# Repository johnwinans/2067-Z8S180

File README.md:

# 2067-Z8S180
Z8S180 Breakout Board

- There is a YouTube playlist that discusses the [Z80-Nouveau](https://www.youtube.com/playlist?list=PL3by7evD3F52rUbThUNDYGxNpKFF1HCNT) project for which this board is an early prototype.
- There is a [Verilog/FPGA YouTube tutorial series](https://www.youtube.com/playlist?list=PL3by7evD3F52On-ws9pcdQuEL-rYbNNFB)
- [Verilog examples](https://github.com/johnwinans/Verilog-Examples) that go along with the above YouTube tutorial.
- This board plugs into the [2057-ICE40HX4K-TQ144-breakout](https://github.com/johnwinans/2057-ICE40HX4K-TQ144-breakout) board.

# Useful DOC

- [Schematic PDF](./2067-Z8S180.pdf)
- [Latest release with gerbers](https://github.com/johnwinans/2067-Z8S180/releases/latest)
- [Z80 CPU User Manual UM008011](https://www.zilog.com/docs/z80/um0080.pdf)
- [Z8S180 Manuals](https://zilog.com/index.php?option=com_product&Itemid=26&task=docs&businessLine=&parent_id=139&familyId=19&productId=Z8S180)
    - [Z8S180 DS0060 - Product Specification](https://www.zilog.com/docs/z180/z8s180ps.pdf)
    - [Z80180 UM0050 - User Manual](https://www.zilog.com/docs/z180/um0050.pdf)

# Revision History

## 1.1 Change CPU footprint to make the pads longer
- add mounting holes
- add labels to the pins on J2

## 1.2 Thermal Relief
- reduce spoke widths
- keep polygon pours off the CPU GND pins
- Connect SRAM A20 to GND w/cuttable track

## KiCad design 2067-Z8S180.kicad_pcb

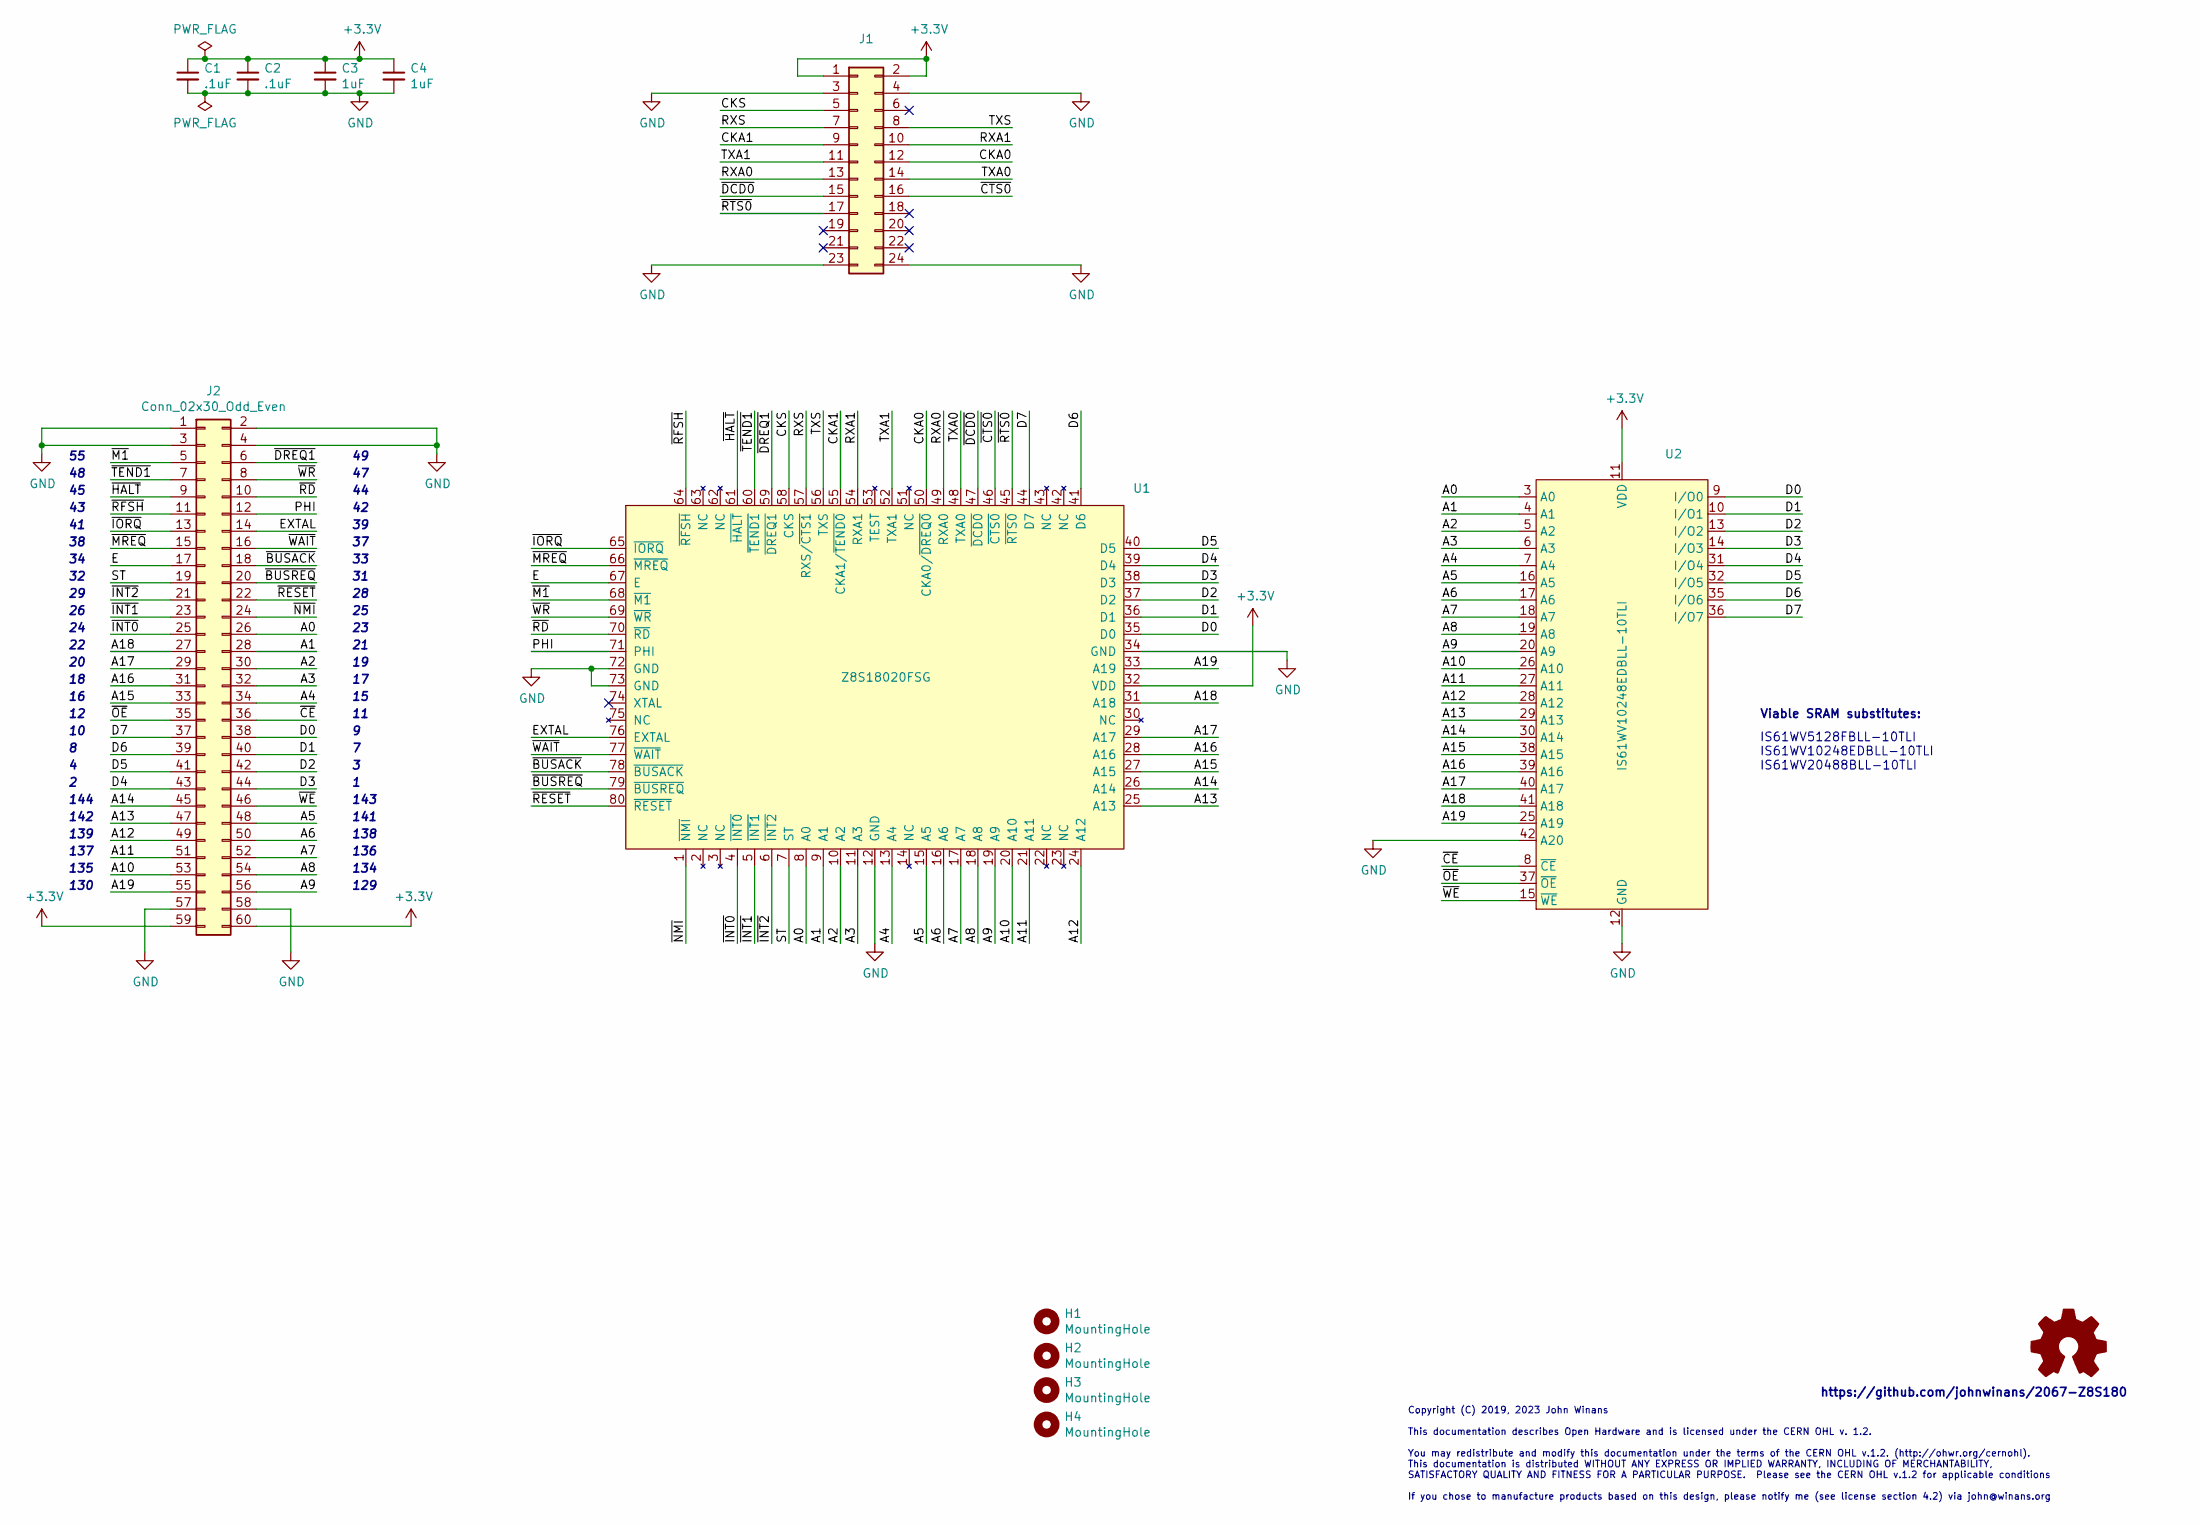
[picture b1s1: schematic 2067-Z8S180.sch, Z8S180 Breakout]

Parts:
C1, C2: .1uF; C_0805_2012Metric_Pad1.15x1.40mm_HandSolder
C3, C4: 1uF; C_0805_2012Metric_Pad1.15x1.40mm_HandSolder
H1, H2, H3, H4: MountingHole; MountingHole_2.7mm_M2.5
J1: Conn_02x12_Odd_Even; PinHeader_2x12_P2.54mm_Vertical
J2: Conn_02x30_Odd_Even; PinHeader_2x30_P2.54mm_Vertical
LOGO1: Logo_Open_Hardware_Small; OSHW-Logo2_9.8x8mm_SilkScreen
U1: Z8S18020FSG; PQFP-80_14x20mm_P0.8mm
U2: IS61WV10248EDBLL-10TLI; TSOP-II-44_10.16x18.41mm_P0.8mm

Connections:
+3V3: C1.1, C2.1, C3.1, C4.1, J1.1, J1.2, J2.59, J2.60, U1.32 (VDD), U2.11 (VDD), U2.33 (VDD)
/A0: J2.26, U1.8 (A0), U2.3 (A0)
/A1: J2.28, U1.9 (A1), U2.4 (A1)
/A2: J2.30, U1.10 (A2), U2.5 (A2)
/A3: J2.32, U1.11 (A3), U2.6 (A3)
/A4: J2.34, U1.13 (A4), U2.7 (A4)
/A5: J2.48, U1.15 (A5), U2.16 (A5)
/A6: J2.50, U1.16 (A6), U2.17 (A6)
/A7: J2.52, U1.17 (A7), U2.18 (A7)
/A8: J2.54, U1.18 (A8), U2.19 (A8)
/A9: J2.56, U1.19 (A9), U2.20 (A9)
/A10: J2.53, U1.20 (A10), U2.26 (A10)
/A11: J2.51, U1.21 (A11), U2.27 (A11)
/A12: J2.49, U1.24 (A12), U2.28 (A12)
/A13: J2.47, U1.25 (A13), U2.29 (A13)
/A14: J2.45, U1.26 (A14), U2.30 (A14)
/A15: J2.33, U1.27 (A15), U2.38 (A15)
/A16: J2.31, U1.28 (A16), U2.39 (A16)
/A17: J2.29, U1.29 (A17), U2.40 (A17)
/A18: J2.27, U1.31 (A18), U2.41 (A18)
/A19: J2.55, U1.33 (A19), U2.25 (A19)
/CKA0: J1.12, U1.50 (CKA0/~DREQ0)
/CKA1: J1.9, U1.55 (CKA1/~TEND0)
/CKS: J1.5, U1.58 (CKS)
/D0: J2.38, U1.35 (D0), U2.9 (I/O0)
/D1: J2.40, U1.36 (D1), U2.10 (I/O1)
/D2: J2.42, U1.37 (D2), U2.13 (I/O2)
/D3: J2.44, U1.38 (D3), U2.14 (I/O3)
/D4: J2.43, U1.39 (D4), U2.31 (I/O4)
/D5: J2.41, U1.40 (D5), U2.32 (I/O5)
/D6: J2.39, U1.41 (D6), U2.35 (I/O6)
/D7: J2.37, U1.44 (D7), U2.36 (I/O7)
/E: J2.17, U1.67 (E)
/EXTAL: J2.14, U1.76 (EXTAL)
/PHI: J2.12, U1.71 (PHI)
/RXA0: J1.13, U1.49 (RXA0)
/RXA1: J1.10, U1.54 (RXA1)
/RXS: J1.7, U1.57 (RXS/~CTS1)
/ST: J2.19, U1.7 (ST)
/TXA0: J1.14, U1.48 (TXA0)
/TXA1: J1.11, U1.52 (TXA1)
/TXS: J1.8, U1.56 (TXS)
/~BUSACK: J2.18, U1.78 (~BUSACK)
/~BUSREQ: J2.20, U1.79 (~BUSREQ)
/~CE: J2.36, U2.8 (~CE)
/~CTS0: J1.16, U1.46 (~CTS0)
/~DCD0: J1.15, U1.47 (~DCD0)
/~DREQ1: J2.6, U1.59 (~DREQ1)
/~HALT: J2.9, U1.61 (~HALT)
/~INT0: J2.25, U1.4 (~INT0)
/~INT1: J2.23, U1.5 (~INT1)
/~INT2: J2.21, U1.6 (~INT2)
/~IORQ: J2.13, U1.65 (~IORQ)
/~M1: J2.5, U1.68 (~M1)
/~MREQ: J2.15, U1.66 (~MREQ)
/~NMI: J2.24, U1.1 (~NMI)
/~OE: J2.35, U2.37 (~OE)
/~RD: J2.10, U1.70 (~RD)
/~RESET: J2.22, U1.80 (~RESET)
/~RFSH: J2.11, U1.64 (~RFSH)
/~RTS0: J1.17, U1.45 (~RTS0)
/~TEND1: J2.7, U1.60 (~TEND1)
/~WAIT: J2.16, U1.77 (~WAIT)
/~WE: J2.46, U2.15 (~WE)
/~WR: J2.8, U1.69 (~WR)
GND: C1.2, C2.2, C3.2, C4.2, J1.3, J1.4, J1.23, J1.24, J2.1, J2.2, J2.3, J2.4, J2.57, J2.58, U1.12 (GND), U1.34 (GND), U1.72 (GND), U1.73 (GND), U2.12 (GND), U2.34 (GND), U2.42 (A20)

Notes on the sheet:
144
142
139
137
135
130
129
134
136
138
141
143
IS61WV5128FBLL-10TLI IS61WV10248EDBLL-10TLI IS61WV20488BLL-10TLI
Viable SRAM substitutes:
Copyright (C) 2019, 2023 John Winans This documentation describes Open Hardware and is licensed under the CERN OHL v. 1.2. You may redistribute and modify this documentation under the terms of the CERN OHL v.1.2. (http://ohwr.org/cernohl). This documentation is distributed WITHOUT ANY EXPRESS OR IM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
https://github.com/johnwinans/2067-Z8S180

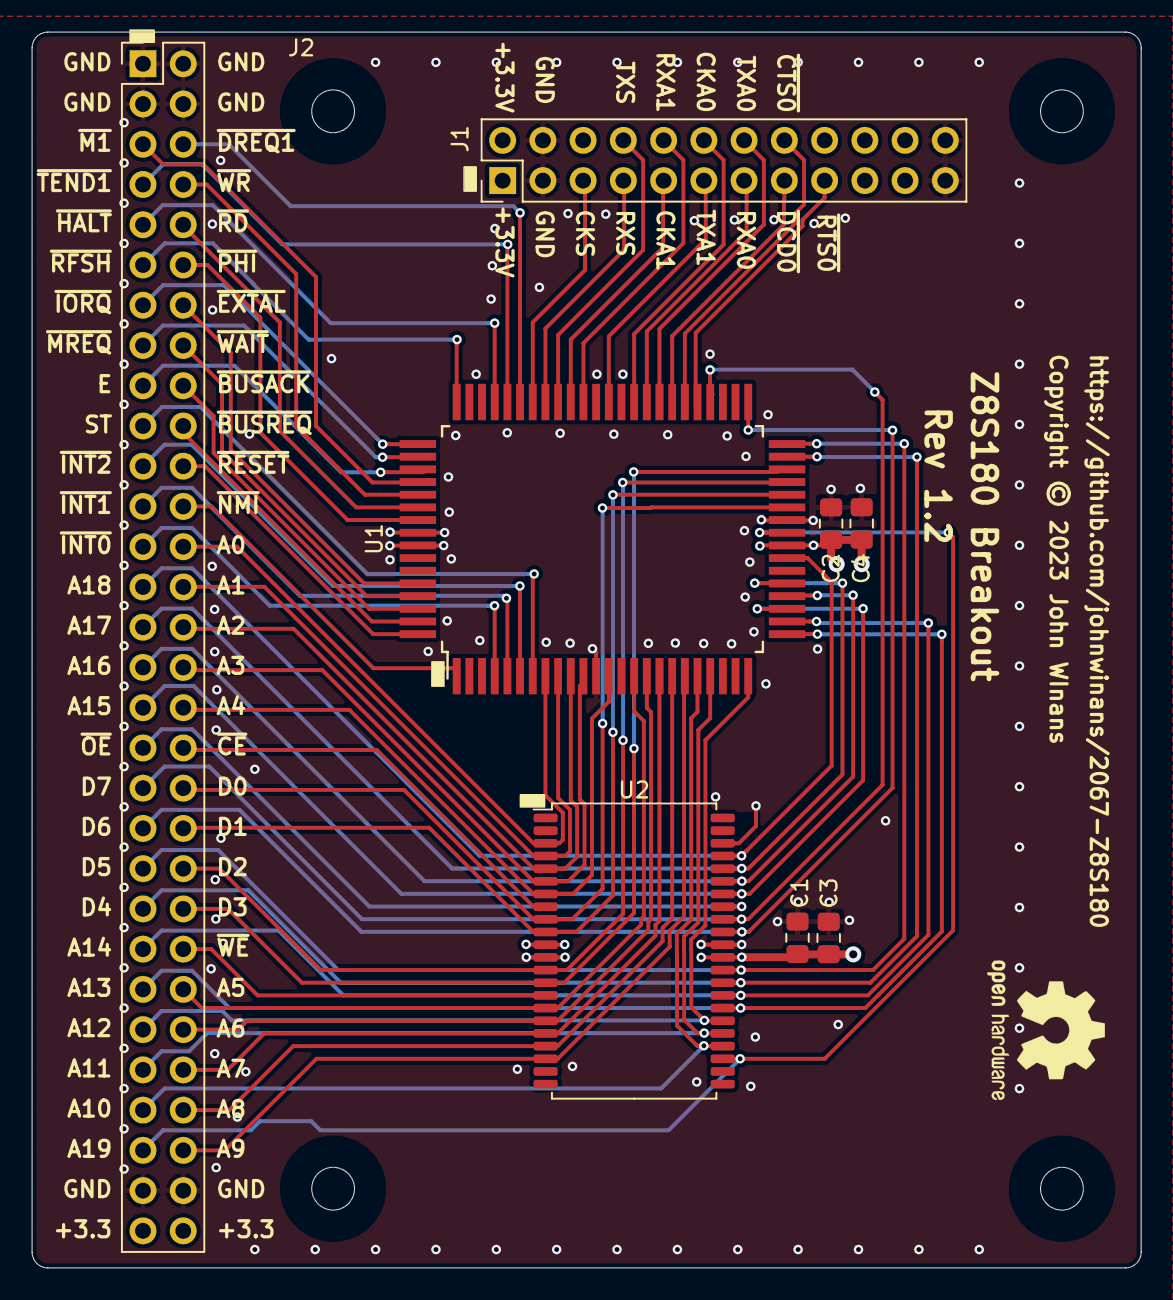
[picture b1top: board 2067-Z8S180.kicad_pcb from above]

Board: 4 copper layers, 70.0 x 78.0 mm, 13 parts (0 on the bottom side), 66 nets.

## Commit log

2023-06-17 Rev 1 import
2023-06-17 Add schematic pdf
2023-06-26 Add image
2023-12-10 Fix CPU footprint, M1/DREQ, and mounting holes
2023-12-10 Update schematic pdf
2023-12-11 Update revision date
2023-12-13 Widen board & add J2 labels
2023-12-13 updated picture
2023-12-13 Rev notes for 1.1
2023-12-13 Add links to playlist & 2057 FPGA board
2024-02-17 Add FPGA pin number reference
2024-02-17 Add reset & NOP tester
2024-02-17 Add missing bits Speed up the clock
2024-02-17 assign outputs for wait, etc
2024-02-17 Change tri-state output ports to inout
2024-02-17 Stub in a boot rom.
2024-02-17 Tweak boot ROM and clock speed
2024-02-17 Clean up loop examples
2024-02-18 typo
2024-02-18 set int_n with 3-bit 111
2024-02-18 Add prog example
2024-02-18 add prog to Makefile & ignore targets
2024-02-18 Move pinmap to TOP & add --freq to nextpnr
2024-02-18 Add FPGA pin numbers for reference
2024-02-18 cleanup for presentation
2024-02-18 Improve consistency with other tests
2024-02-19 Pass interesting signals through to probable pins
2024-02-19 Add a warning about why this code actually works
2024-02-19 Make interesting signals probable
2024-02-19 Add some test-point signals on bottom header
2024-02-19 Pass interesting signals to test points
2024-02-19 whitespace
2024-02-19 Note the restriction on this code on the 180
2024-02-19 Remove redundant port signals :-(
2024-02-19 Comment the OUT0 situation
2024-02-20 Add a simple SRAM tester
2024-02-20 cleanup for video recording
2024-02-20 Add/fix doc
2024-02-20 Notes for Rel 1.2 & doc links
2024-02-20 Thermal relief, SRAM A20
2024-02-20 Doc the ports
2024-02-20 Change OUT to OUT0
2024-02-20 Run SRAM async
2024-02-21 Use OUT0 instructions
2024-02-21 Fix broken OUT0
2024-02-24 Use OUT0 instead of OUT
2024-02-24 Wordsmithing
2024-02-24 typos in doc
2024-02-26 Add comments
2024-02-26 Use PHI rather than HWCLK for BRAM
2024-02-26 Update manual links to newer versions
2024-02-26 cleanuo
2024-05-18 ASCI test program
2024-05-22 Add first draft of nouveau
2024-05-22 Add a PLL to generate 18.432MHZ for simple bit rates
2024-05-26 Correct a comment location
2024-05-26 Remove unused
2024-11-25 propagate phi, e, iorq_n through to test pins
2025-01-10 Add notes about the S180 default IO address map
2025-01-12 Add iorq_fsm.v to synchronize CPU IO w/FPGA
2025-01-12 As seen on YouTube 20250112.1
2025-01-12 copy nouveau2 for a memory test
2025-01-13 WHAT WAS I SMOKING?
2025-01-13 Almost as seen on YouTube 20250112.2
2025-01-13 How manu buts are in a bit?
2025-01-14 Clean up doc, timing, and address decoders
2025-01-14 make ioreq_rd_j4 use iorq_rd (not _wr)
2025-01-14 Refresh from nouveau2
2025-01-14 Note problematic PLL pins
2025-01-18 Unify pcf files
2025-01-18 unified pcf file
2025-01-18 Add an example of a memory-mapped BRAM
2025-01-18 add nouveau[23]
2025-01-18 Replicate nouveau3 as a starting point
2025-01-18 Unify the make rules & local overrides
2025-01-18 whitespace fix
2025-01-18 might need this!
2025-01-18 use CROSS_AS for the z80 compiler
2025-01-18 Add VDP_LIBV in case it becomes useful
2025-01-18 nouveau-vdp proof of concept of VDP hwclk
2025-01-19 Doc the purpose of this directory.
2025-01-19 formatting
2025-01-19 Doc purpose of this version of the nouveau
2025-01-19 Doc purpose of this directory
2025-01-19 Assert reset whilst PLL is starting & unstable
2025-01-19 Compile changes to allow use of other yosys and nextpnr platform tools for FPGA's other than ice40
2025-01-19 Fix reset signal bug
2025-01-25 Move the IO memory map to a place that makes sense.
2025-01-25 nouveau2 code fork for multi-clock domaion interface
2025-01-25 cleanup
2025-01-28 Remove bram test noise
2025-01-28 86 the IO memory map noise in the README
2025-01-29 Rephrase misleading doc
2025-01-31 Control regs for a TI99 style VDP
2025-02-01 Ignore vim swap files
2025-02-01 Narrow name of the VDP control reg module
2025-02-01 Name & doc cleanup
2025-02-01 Add an IRQ generator
2025-02-01 cobble together a tb to compile-check vdp99.v
2025-02-01 Rename cpu-interface to nouveau-vdp99
2025-02-01 Add Make.include files make deps easier
2025-02-01 Make names consistent
2025-02-02 Refactor iorq fsm modules into a new library Clean up Makefiles Add z80_wr_cdc.v
2025-02-02 Clean up makefiles
2025-02-02 Add vdp and vdp99 mainly for make clean
2025-02-02 Refactor iorq stuff to library
2025-02-02 Dev checkpoint
2025-02-02 Parameterize the width of the address bus
2025-02-04 cosmetic
2025-02-04 Yosys doesn't like my wr_tick1 D-latch :-(
2025-02-04 test case writes all 8 VDP config regs
2025-02-04 Add note about a test program for this dev checkpont
2025-02-05 Add --ignore-loops to nextpnr for D-Latch problem
2025-02-08 Update the flash batch file to use pinctrl
2025-02-08 Remove --ignore-loops, we're going synchronous
2025-02-08 Cleanup test case with sane timing values
2025-02-08 add a delayed nonblocking rhs eval test
2025-02-08 As seen on YouTube
2025-02-09 clean up test bench
2025-02-09 Note purpose
2025-02-09 Simplify sync, test @ worst case timing
2025-02-09 Add vgasync.v to vdp99_tb build
2025-02-09 rethink rd/wr_tick, use last_pixel for irq, send frame flag to dout
2025-02-09 Change how rd/wr_tick works
2025-02-09 Add last_pixel flag
2025-02-09 implement ioreq_rd_vdp, int_n[2] = vdp_irq
2025-02-09 stretch vdp_dout
2025-02-09 86 the ioreq_rd/wr_vdp_ticks, extend test to a full video frame
2025-02-11 Add TI99 style borders to vgasync
2025-02-11 Add a waveform diag of the vdp99 FSM
2025-02-11 ignore targets
2025-02-12 capture the VDP mode when either reading or writing
2025-02-13 ++i not portable
2025-02-15 Added vram module
2025-02-15 corrected doc
2025-02-15 Discard VRAM register writes.
2025-02-15 reset addr_state_next when read status reg don't update addr reg when write to vdp reg
2025-02-15 Add VRAM to the VDP
2025-02-15 Add DMA access to the VRAM for reading
2025-02-16 Clean up time reference
2025-02-16 Add vdp FSM
2025-02-16 incorporate the VDP FSM
2025-02-17 pixel-doubling cols & rows
2025-02-17 fix pipeline propagation delay
2025-02-17 row-doubling bug
2025-02-17 Fix missing vram init image
2025-02-17 change when to advance tile_counter to next row
2025-02-17 error in color attribute address calc
2025-02-17 Make the VRAM size a configurable parameter
2025-02-17 Add support for display blank bit in reg 1
2025-02-17 try running in the right gfx mode!
2025-02-17 Add first drafts of other VDP modes
2025-02-17 Shrink RAM for boot ROM & put into VRAM
2025-02-18 set the bgcolor to the... bgcolor!
2025-02-18 keep ring_ctr in phase when a new px_row starts
2025-02-19 add text mode padding logic to vgasync
2025-02-19 Add IE bit in VDP register 1
2025-02-19 Test the VDP IE bit
2025-02-20 Reset VDP regs on... reset
2025-02-20 Shut off text mode
2025-02-20 stat reg report end of frame, not IRQ pin state
2025-02-22 Change from 3 to 6-bit VGA analog outputs
2025-02-22 Add TI99-ish color palette
2025-02-22 change wire to reg as appropriate
2025-02-23 fix test bench deps
2025-02-23 Standardize sim target names
2025-02-23 Resistor DAC values for VGA color bits
2025-02-23 Also note the resisors used on hsync & vsync
2025-02-23 Use BG color if a pixel is transparent
2025-02-24 Change bad parameter name
2025-02-24 Infer even number of BRAMs due to yosys bug
2025-02-26 fix broken video link
2025-02-28 Replace sysfs GPIO yick with gpioset/get
2025-03-01 Note impact on pxclk speed limit
2025-03-01 Delay VRAM CPU read cycles by one pxclk
2025-03-02 Run simulation into second frame
2025-03-02 Use only one VRAM read cycle when request DMA
2025-03-02 Clarify where the row & col origins are
2025-03-05 Add sprite_tick to signal optimal sprite load time
2025-03-05 Config GM1 w/sprites
2025-03-05 Add sprite attribute table
2025-03-09 Stub-in sprite-fetching logic
2025-03-09 Make tb build consistently w/inherit timescale
2025-03-09 Remove stale comment
2025-03-16 Comment on vdp99.rd_tick relationship to vdp99.dma_rd_tick
2025-03-16 Correct doc
2025-03-18 Add sprite.v
2025-05-03 Remove the big port
2025-06-29 untillllll
2025-06-30 Add more tests
2025-07-01 Add a dma+read conflict case
2025-07-27 Adjust to as-built FSM timing
2025-08-16 Nuke redundant clean rule
2025-08-16 define no default net type & timescale
2025-08-16 shut up timescale crap
2025-08-16 timescale
2025-08-17 nuke the rom.hex file in the clean rule
2025-08-17 vdp99/vdp_fsm.v refactor checkpoint
2025-08-17 sprite fsm refactor
2025-08-18 pre-proc z80_vdp99_tb.ram.in and add comments
2025-08-21 change filename hardcode to __FILE__
2025-08-24 First viable version
2025-08-27 Add sprite controllers
2025-08-30 checkpoint
2025-08-30 sprite dev checkpoint
2025-08-30 Add a pipeline-delayed sprite_tick_out
2025-08-30 Shut up pointless yosys noise
2025-08-31 Stub in joystick inputs
2025-08-31 Remove pre-palette mapping hack
2025-08-31 Use vdp_smag properly
2025-08-31 Add hpos_phase_reg to shift from even/odd hops
2025-08-31 sprite mag works
2025-08-31 sprite 16x16 size works
2025-09-02 Add collision & 5th sprite status
2025-09-04 fifth_flag_next bug ony check colisions during active region
2025-09-04 multicolor mode
2025-09-05 Add a joystick input
2025-09-05 Add VDP IRQ status to port A8 (a'la Retro!)
2025-09-05 in or out... make up your mind!!!
2025-09-05 load the color_reg at the correct time :-)
2025-09-05 row used for multicolr was off by 6
2025-09-07 Add prescaler
2025-09-07 stub in graphics mode 4 test values
2025-09-07 Add crc
2025-09-07 Add ay_noise
2025-09-07 Add ay_regs
2025-09-07 Add ay3891x stub with noise generator
2025-09-07 the ay3891x is doing.... something
2025-09-07 output 1 when disabled
2025-09-07 integrate ay-3-8910
2025-09-08 Make prescaler sane
2025-09-09 Added ay_adc & pwm
2025-09-09 reduce max pwm period to 111
2025-09-09 Fix signal-width
2025-09-09 hold reset active when signal is low
2025-09-09 correct the use of ay_clk
2025-09-10 Stub in code/comment to OR the three PWMs into one output bit
2025-09-11 Added an envelope generator
2025-09-11 re-endianize the envelope period
2025-09-12 Add z80_ay3891x to synchronize cpu & ay clock domains
2025-09-12 apply basic algebra :-)
2025-09-12 clean up timing
2025-09-12 fix broken algebra
2025-09-14 Remove bad comma
2025-09-14 sim check sprite & gfx not access VRAM at same time
2025-09-21 fix doc
2025-09-21 correct comment
2025-09-21 fix SAT scan termination logic
2025-09-23 Add memory map
2025-09-23 Saner prescaler values
2025-09-26 temp hack fix of the envelope clock wrong speed
2025-09-27 remove prescaler brain damage
2025-09-27 test bench tweaks
2025-09-28 doc simplify EC math
2025-10-04 Run VGA signals through sync latch to compensate for prio encoders
2025-10-05 un-do the sync latch (move elsewhere)
2025-10-05 refactor top.v, sync vga signals to pxclk
2025-10-06 update 5th sprite num in stat reg while scan unless flag set
2025-11-15 Doc cleanup
2025-12-28 Deal with libgpio update in progress. Tested on Bookworm & Trixie
2025-12-28 Remove blif & arachne cruft

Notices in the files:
2067-Z8S180.kicad_pcb:
Copyright © 2023 John WInans
2067-Z8S180.sch:
If you chose to manufacture products based on this design, please notify me (see license section 4.2) via john@winans.org
